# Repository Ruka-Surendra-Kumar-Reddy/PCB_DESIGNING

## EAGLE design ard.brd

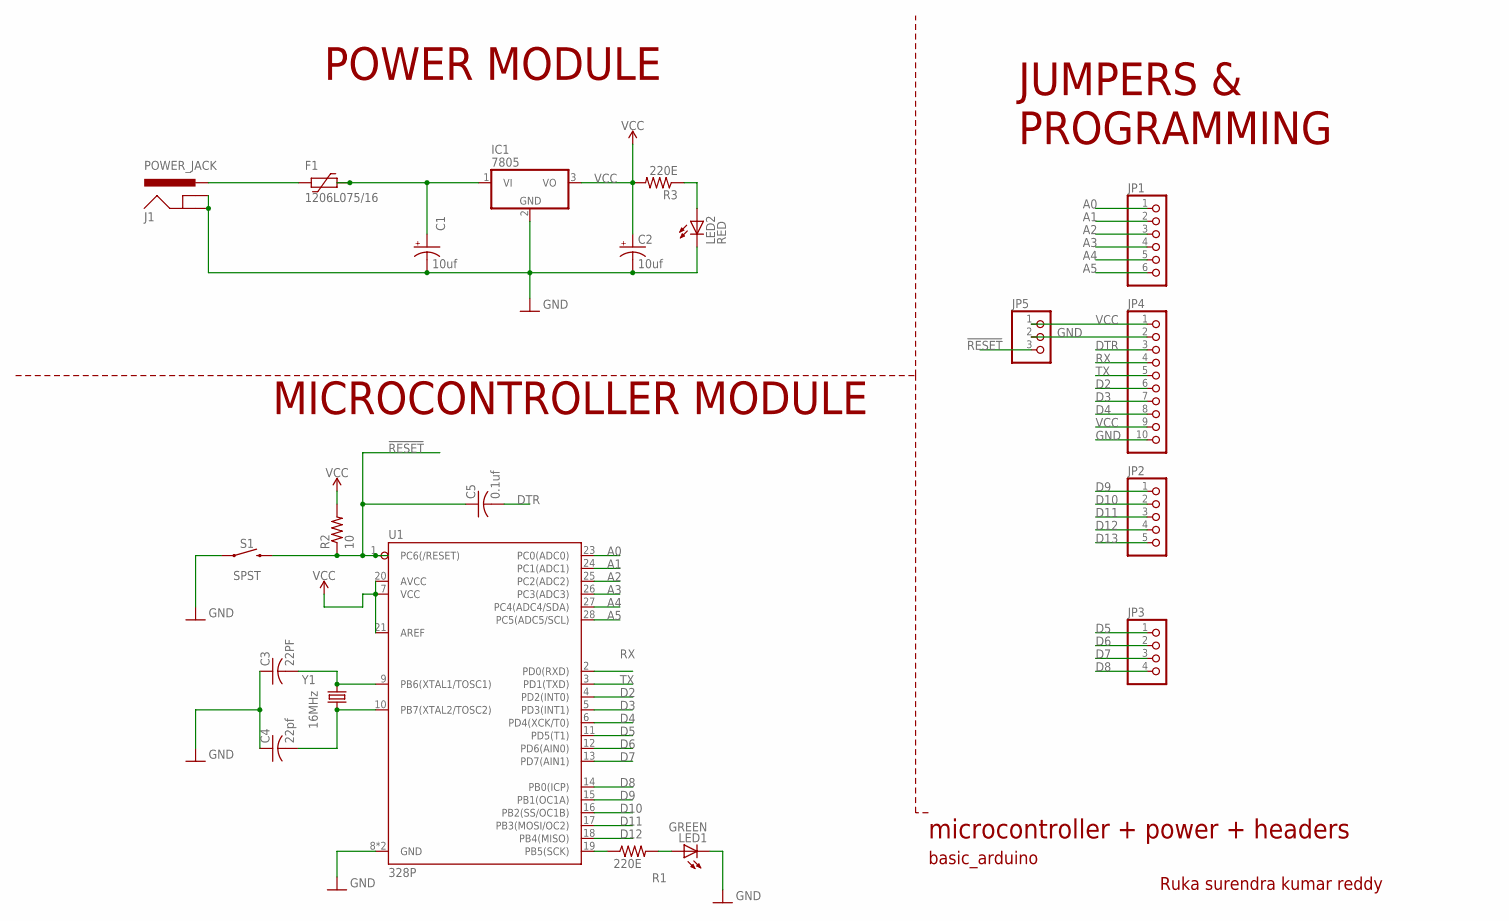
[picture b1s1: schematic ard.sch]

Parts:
C1, C2: 10uf; E2,5-6E
C3: 22PF; C025-024X044
C4: 22pf; C025-024X044
C5: 0.1uf; C025-024X044
F1: 1206L075/16; 1206L
IC1: 7805; TO220V
J1: POWER_JACK; POWER_JACK_PTH
JP1: PINHD-1X6; 1X06
JP2: PINHD-1X5; 1X05
JP3: PINHD-1X4; 1X04
JP4: PINHD-1X10; 1X10
JP5: PINHD-1X3; 1X03
LED1: GREEN; LED5MM
LED2: RED; LED5MM
R1, R3: 220E; 0204/7
R2: 10; 0204/7
S1: SPST; TACTILE_SWITCH_PTH_6.0MM
U1: 328P; DIP28
Y1: 16MHz; HC49US

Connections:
!RESET: C5.1, JP5.3, R2.1, S1.3 (2), U1.1 (PC6(/RESET))
A0: JP1.1, U1.23 (PC0(ADC0))
A1: JP1.2, U1.24 (PC1(ADC1))
A2: JP1.3, U1.25 (PC2(ADC2))
A3: JP1.4, U1.26 (PC3(ADC3))
A4: JP1.5, U1.27 (PC4(ADC4/SDA))
A5: JP1.6, U1.28 (PC5(ADC5/SCL))
D2: JP4.6, U1.4 (PD2(INT0))
D3: JP4.7, U1.5 (PD3(INT1))
D4: JP4.8, U1.6 (PD4(XCK/T0))
D5: JP3.1, U1.11 (PD5(T1))
D6: JP3.2, U1.12 (PD6(AIN0))
D7: JP3.3, U1.13 (PD7(AIN1))
D8: JP3.4, U1.14 (PB0(ICP))
D9: JP2.1, U1.15 (PB1(OC1A))
D10: JP2.2, U1.16 (PB2(SS/OC1B))
D11: JP2.3, U1.17 (PB3(MOSI/OC2))
D12: JP2.4, U1.18 (PB4(MISO))
D13: JP2.5, R1.1, U1.19 (PB5(SCK))
DTR: C5.2, JP4.3
GND: C1.-, C2.-, C3.1, C4.1, IC1.2 (GND), J1.GND, J1.GNDBREAK, JP4.2, JP4.10, JP5.2, LED1.K (C), LED2.K (C), S1.1, U1.8 (GND), U1.22 (GND)
unnamed: C3.2, U1.9 (PB6(XTAL1/TOSC1)), Y1.1
unnamed: C4.2, U1.10 (PB7(XTAL2/TOSC2)), Y1.2
unnamed: C1.+, F1.1, IC1.1 (VI)
unnamed: LED1.A, R1.2
unnamed: F1.2, J1.PWR
unnamed: LED2.A, R3.1
RX: JP4.4, U1.2 (PD0(RXD))
TX: JP4.5, U1.3 (PD1(TXD))
VCC: C2.+, IC1.3 (VO), JP4.1, JP4.9, JP5.1, R2.2, R3.2, U1.7 (VCC), U1.20 (AVCC), U1.21 (AREF)

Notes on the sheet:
POWER MODULE
JUMPERS & PROGRAMMING
MICROCONTROLLER MODULE
basic_arduino
Ruka surendra kumar reddy
microcontroller + power + headers

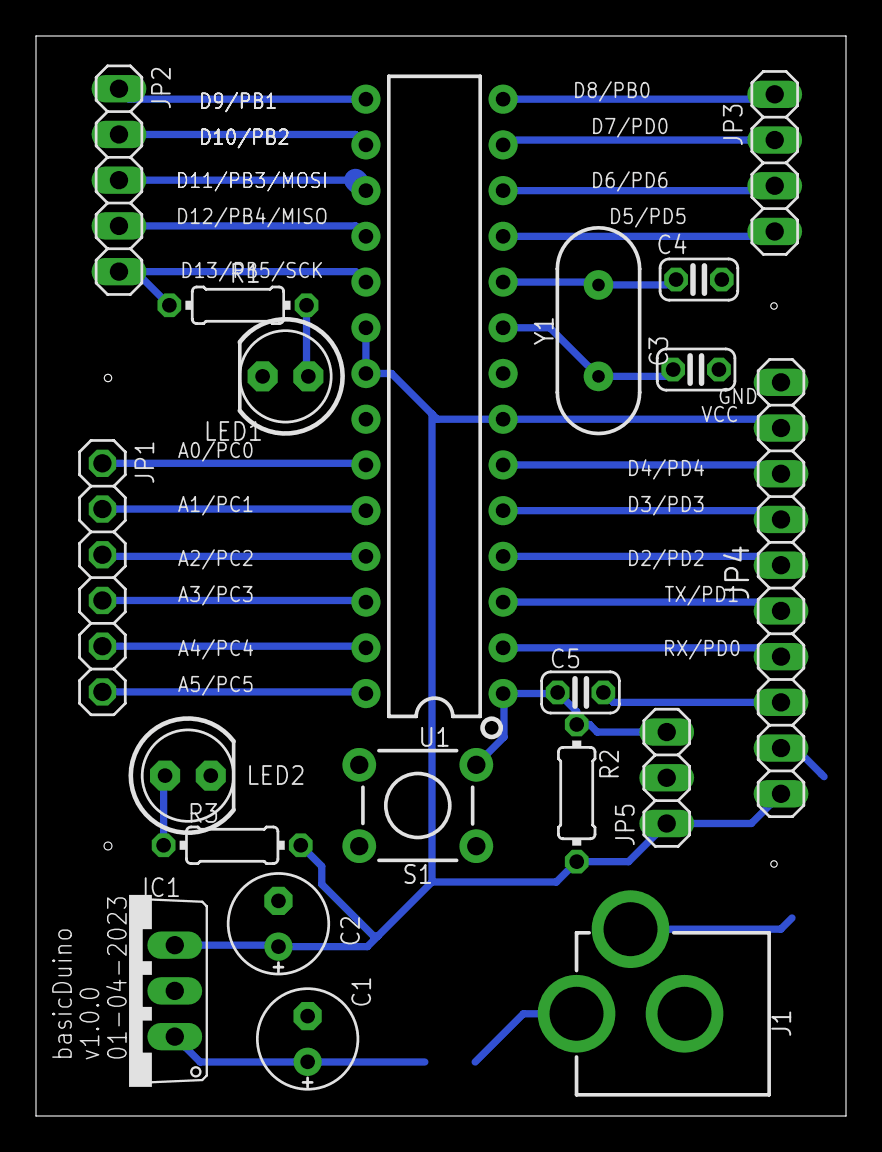
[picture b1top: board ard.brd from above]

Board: 2 copper layers, 45.0 x 60.0 mm, 21 parts (1 on the bottom side), 30 nets.

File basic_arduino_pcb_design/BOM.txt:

Qty Value       Device                          Package                  Parts  Description                              
1               PINHD-1X10                      1X10                     JP4    PIN HEADER                                                                                                                             
1               PINHD-1X3                       1X03                     JP5    PIN HEADER                                                                                                                             
1               PINHD-1X4                       1X04                     JP3    PIN HEADER                                                                                                                               
1               PINHD-1X5                       1X05                     JP2    PIN HEADER                                                                                                                             
1               PINHD-1X6                       1X06                     JP1    PIN HEADER                                                                                                                                   
1   0.1uf       C-US025-024X044                 C025-024X044             C5     CAPACITOR, American symbol                                                                                                          
1   10          R-US_0204/7                     0204/7                   R2     RESISTOR, American symbol                                                                                                             
2   10uf        CPOL-USE2,5-6E                  E2,5-6E                  C1, C2 POLARIZED CAPACITOR, American symbol                                                                                                     
1   1206L075/16 1206L075/16                     1206L                    F1     Polyfuse Resettable PTC                                                                             
1   16MHz       CRYSTAL-16MHZPTH-HC49US         HC49US                   Y1     16MHz Crystal                                                                                                     
2   220E        R-US_0204/7                     0204/7                   R1, R3 RESISTOR, American symbol                                                                                                                
1   22PF        C-US025-024X044                 C025-024X044             C3     CAPACITOR, American symbol                                                                                                                
1   22pf        C-US025-024X044                 C025-024X044             C4     CAPACITOR, American symbol                                                                                                                
1   328P        ATMEGA328P_PDIP                 DIP28                    U1     Atmel 328P                                                                                                                    
1   7805        7805TV                          TO220V                   IC1    Positive VOLTAGE REGULATOR                                                                                                              
1   GREEN       LED5MM                          LED5MM                   LED1   LED                                                                                                                                          
1   POWER_JACK  POWER_JACK                      POWER_JACK_PTH           J1     Power Jack Connector                                                                                                               
1   RED         LED5MM                          LED5MM                   LED2   LED                                                                                                                                          
1   SPST        MOMENTARY-SWITCH-SPST-PTH-6.0MM TACTILE_SWITCH_PTH_6.0MM S1     Momentary Switch (Pushbutton) - SPST

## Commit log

2023-04-11 Create GERBERS

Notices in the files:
parts and their libraries:
SparkFun-Connectors: Licensing: Creative Commons ShareAlike 4.0 International - https://creativecommons.org/licenses/by-sa/4.0
